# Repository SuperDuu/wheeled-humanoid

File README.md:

# Wheeled Humanoid Robot (V2)

A custom-designed wheeled humanoid robot featuring a mobile base, dual humanoid arms, custom cycloidal drives, custom motor drivers, and integrated with ROS 2, Computer Vision, and AI.

## Project Structure

- **docs/**: Project documentation, communication protocols, and datasheets.
- **hardware/**: Mechanical CAD designs (SolidWorks/STEP) and electronic PCBs (KiCad).
- **firmware/**: Low-level MCU source code for controllers and motor drivers.
- **software/**: High-level ROS 2 packages and AI/Vision algorithms.
- **legacy/**: Submodule containing Version 1 of the AGV project (`agv_project`).

## Quick Start

### Submodule Initialization
If you just cloned this repository, initialize the legacy v1 submodule:
```bash
git submodule update --init --recursive
```

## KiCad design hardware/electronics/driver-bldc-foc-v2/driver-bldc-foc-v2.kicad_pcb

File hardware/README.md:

# Hardware Designs

This directory contains mechanical and electrical engineering designs.

- **mechanical/**: CAD models, cycloidal gear designs, assembly models, and 3D print files.
- **electronics/**: KiCad schematics and layout designs for custom motor drivers and power boards.

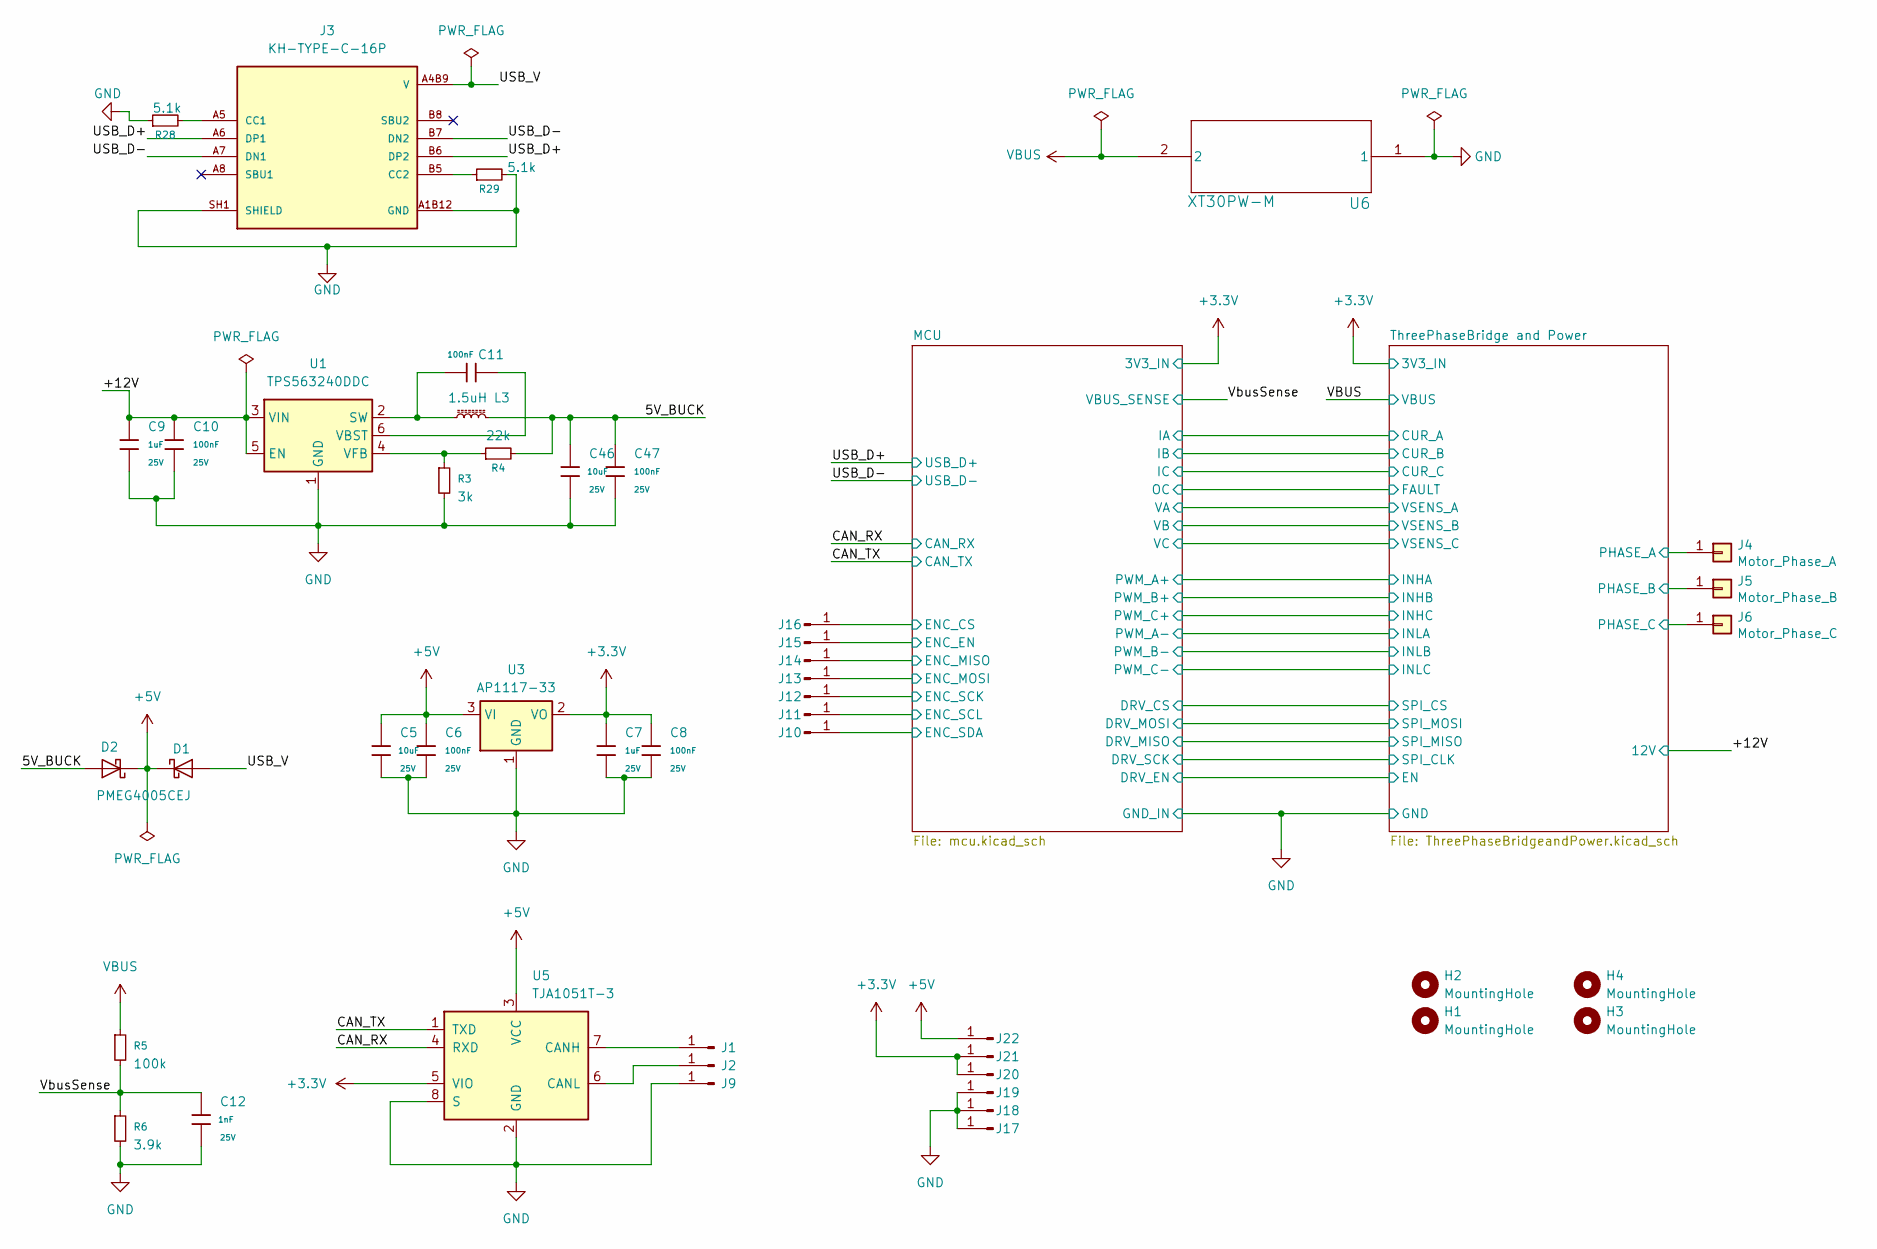
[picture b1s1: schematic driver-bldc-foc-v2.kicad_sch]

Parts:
C5, C46: 10uF; C_0805_2012Metric; Voltage Rated 25V; Tolerance ±10%; Part CL21A106KAYNNNE; LCSC C15850
C6, C8, C10, C11, C47: 100nF; C_0805_2012Metric; Voltage Rated 25V; Tolerance ±10%; Part CL21A106KAYNNNE; LCSC C15850
C7, C9: 1uF; C_0805_2012Metric; Voltage Rated 25V; Tolerance ±10%; Part CL21A106KAYNNNE; LCSC C15850
C12: 1nF; C_0805_2012Metric; Voltage Rated 25V; Tolerance ±10%; Part CL21A106KAYNNNE; LCSC C15850
D1, D2: PMEG4005CEJ; D_SOD-323F
H1, H2, H3, H4: MountingHole; MountingHole_3.2mm_M3_ISO7380_Pad_TopBottom
J1, J2, J9, J10, J11, J12, J13, J14, J15, J16, J17, J18, J19, J20, J21, J22: Conn_01x01_Pin; SolderWirePad_1x01_SMD_2x4mm
J3: KH-TYPE-C-16P; KINGHELM_KH-TYPE-C-16P; PARTREV A0
J4: Motor_Phase_A; SolderWirePad_1x01_SMD_5x10mm
J5: Motor_Phase_B; SolderWirePad_1x01_SMD_5x10mm
J6: Motor_Phase_C; SolderWirePad_1x01_SMD_5x10mm
L3: 1.5uH; L_APV_ANR5040
R3: 3k; R_0805_2012Metric
R4: 22k; R_0805_2012Metric
R5: 100k; R_0805_2012Metric
R6: 3.9k; R_0805_2012Metric
R28, R29: 5.1k; R_0805_2012Metric
U1: TPS563240DDC; SOT-23-6
U3: AP1117-33; SOT-223-3_TabPin2
U5: TJA1051T-3; SOIC-8_3.9x4.9mm_P1.27mm
U6: XT30PW-M; XT30PW-M_AMA

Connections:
+3.3V: C7.1, C8.1, J20.1 (Pin_1_1), J21.1 (Pin_1_1), U3.2 (VO), U5.5 (VIO); also elsewhere on the board
+5V: C5.1, C6.1, D1.1 (K), D2.1 (K), J22.1 (Pin_1_1), U3.3 (VI), U5.3 (VCC)
/5V_BUCK: C46.1, C47.1, D2.2 (A), L3.2, R4.2
/+12V: C9.1, C10.1, U1.3 (VIN), U1.5 (EN); also elsewhere on the board
/CAN_RX: U5.4 (RXD); also elsewhere on the board
/CAN_TX: U5.1 (TXD); also elsewhere on the board
/MCU/ENC_CS: J16.1 (Pin_1_1); also elsewhere on the board
/MCU/ENC_EN: J15.1 (Pin_1_1); also elsewhere on the board
/MCU/ENC_MISO: J14.1 (Pin_1_1); also elsewhere on the board
/MCU/ENC_MOSI: J13.1 (Pin_1_1); also elsewhere on the board
/MCU/ENC_SCK: J12.1 (Pin_1_1); also elsewhere on the board
/MCU/ENC_SCL: J11.1 (Pin_1_1); also elsewhere on the board
/MCU/ENC_SDA: J10.1 (Pin_1_1); also elsewhere on the board
/ThreePhaseBridge and Power/SHA: J4.1 (Pin_1_1); also elsewhere on the board
/ThreePhaseBridge and Power/SHB: J5.1 (Pin_1_1); also elsewhere on the board
/ThreePhaseBridge and Power/SHC: J6.1 (Pin_1_1); also elsewhere on the board
/USB_D+: J3.A6 (DP1), J3.B6 (DP2); also elsewhere on the board
/USB_D-: J3.A7 (DN1), J3.B7 (DN2); also elsewhere on the board
/VbusSense: C12.1, R5.2, R6.1; also elsewhere on the board
GND: C5.2, C6.2, C7.2, C8.2, C9.2, C10.2, C12.2, C46.2, C47.2, J3.A1B12 (GND), J3.A12B1 (GND), J3.SH1 (SHIELD), J3.SH2 (SHIELD), J3.SH3 (SHIELD), J3.SH4 (SHIELD), J9.1 (Pin_1_1), J17.1 (Pin_1_1), J18.1 (Pin_1_1), J19.1 (Pin_1_1), R3.2, R6.2, R28.1, R29.2, U1.1 (GND), U3.1 (GND), U5.2 (GND), U5.8 (S), U6.1; also elsewhere on the board
unnamed: J1.1 (Pin_1_1), U5.7 (CANH)
unnamed: J2.1 (Pin_1_1), U5.6 (CANL)
unnamed: J3.A5 (CC1), R28.2
unnamed: J3.B5 (CC2), R29.1
unnamed: C11.2, L3.1, U1.2 (SW)
unnamed: C11.1, U1.6 (VBST)
unnamed: R3.1, R4.1, U1.4 (VFB)
V: D1.2 (A), J3.A4B9 (V), J3.A9B4 (V)
VBUS: R5.1, U6.2; also elsewhere on the board

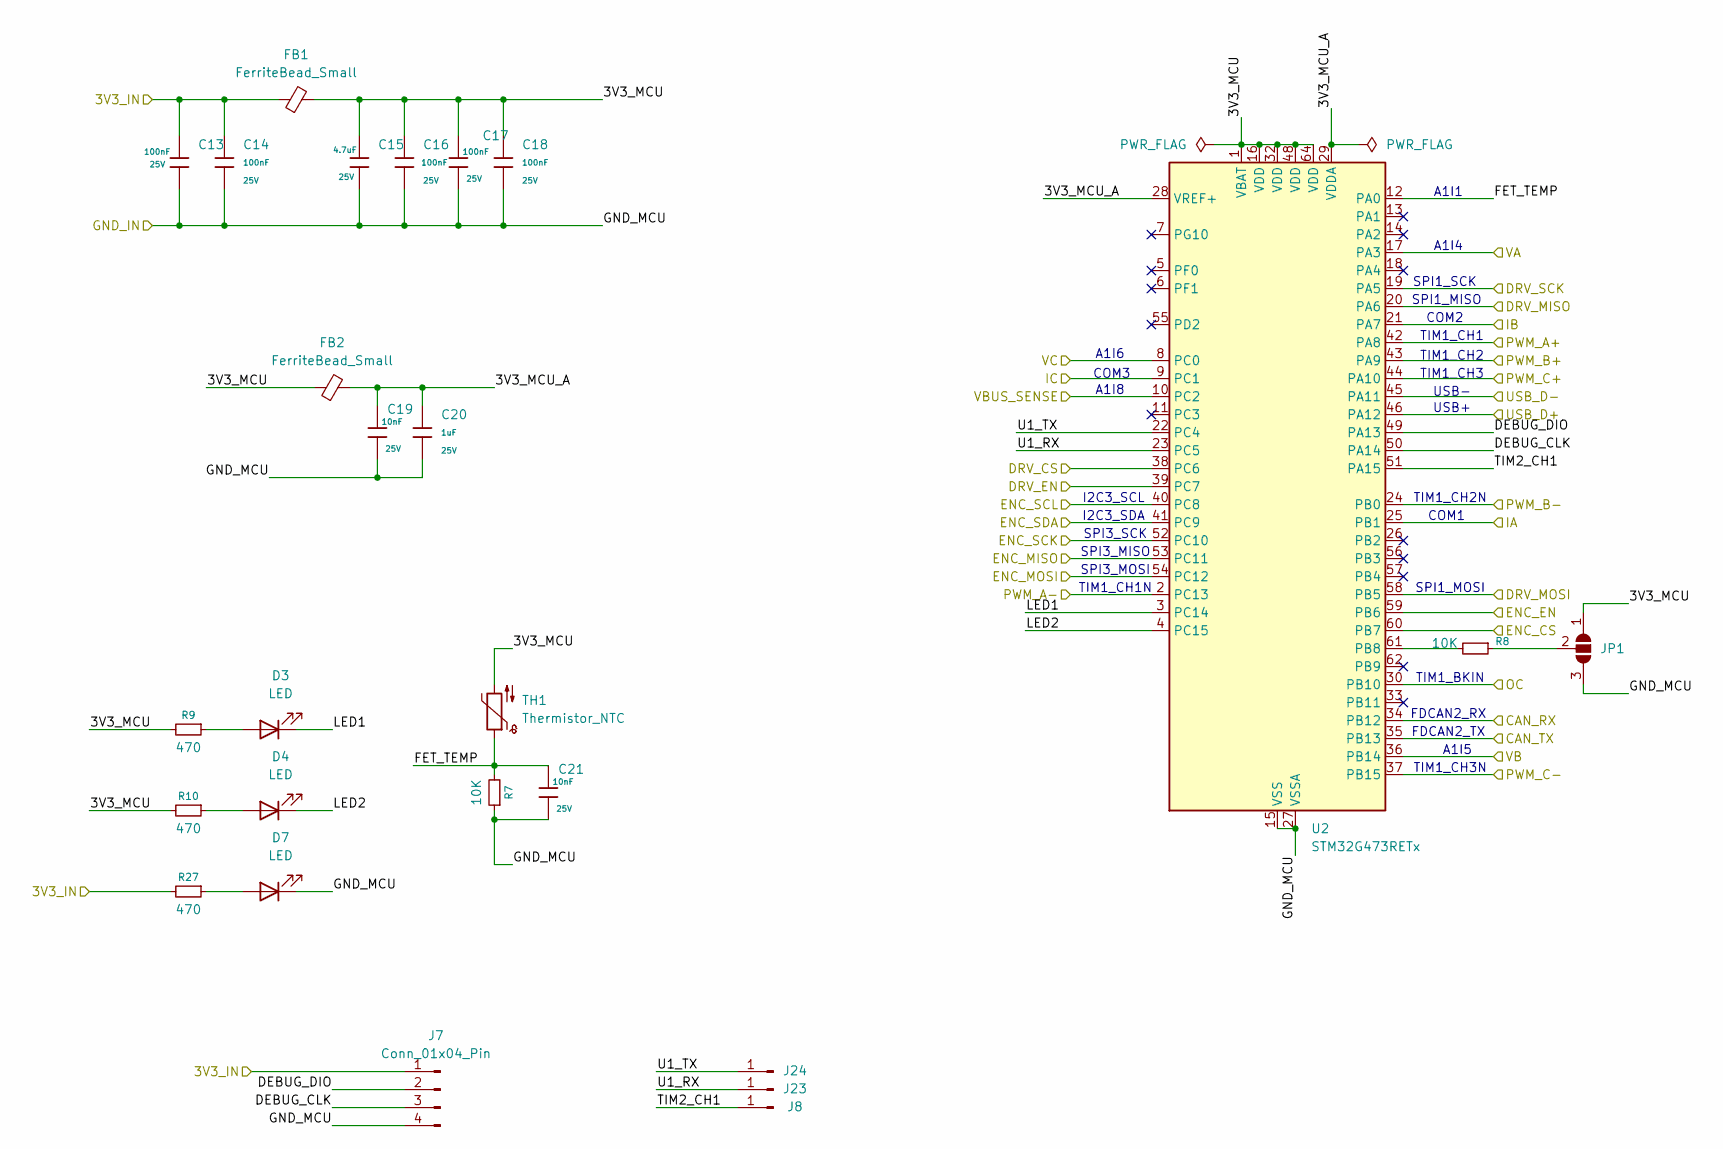
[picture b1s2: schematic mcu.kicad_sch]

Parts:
C13, C14, C16, C17, C18: 100nF; C_0805_2012Metric; Voltage Rated 25V; Tolerance ±10%; Part CL21A106KAYNNNE; LCSC C15850
C15: 4.7uF; C_0805_2012Metric; Voltage Rated 25V; Tolerance ±10%; Part CL21A106KAYNNNE; LCSC C15850
C19, C21: 10nF; C_0805_2012Metric; Voltage Rated 25V; Tolerance ±10%; Part CL21A106KAYNNNE; LCSC C15850
C20: 1uF; C_0805_2012Metric; Voltage Rated 25V; Tolerance ±10%; Part CL21A106KAYNNNE; LCSC C15850
D3, D4, D7: LED; LED_0805_2012Metric
FB1, FB2: FerriteBead_Small; L_0603_1608Metric_Pad1.05x0.95mm_HandSolder
J7: Conn_01x04_Pin; JST_XH_B4B-XH-A_1x04_P2.50mm_Vertical
J8, J23, J24: Conn_01x01_Pin; SolderWirePad_1x01_SMD_1x2mm
JP1: SolderJumper_3_Open; SolderJumper-3_P1.3mm_Open_RoundedPad1.0x1.5mm_NumberLabels
R7, R8: 10K; R_0805_2012Metric
R9, R10, R27: 470; R_0805_2012Metric
TH1: Thermistor_NTC; R_Axial_DIN0204_L3.6mm_D1.6mm_P1.90mm_Vertical
U2: STM32G473RETx; LQFP-64_10x10mm_P0.5mm

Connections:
+3.3V: C13.1, C14.1, FB1.1, J7.1, R27.2; also elsewhere on the board
/CAN_RX: U2.34 (PB12); also elsewhere on the board
/CAN_TX: U2.35 (PB13); also elsewhere on the board
/MCU/3V3_MCU: C15.1, C16.1, C17.1, C18.1, FB1.2, FB2.1, JP1.1 (A), R9.2, R10.2, TH1.2, U2.1 (VBAT), U2.16 (VDD), U2.32 (VDD), U2.48 (VDD), U2.64 (VDD)
/MCU/3V3_MCU_A: C19.1, C20.1, FB2.2, U2.28 (VREF+), U2.29 (VDDA)
/MCU/DEBUG_CLK: J7.3, U2.50 (PA14)
/MCU/DEBUG_DIO: J7.2, U2.49 (PA13)
/MCU/DRV_CS: U2.38 (PC6); also elsewhere on the board
/MCU/DRV_EN: U2.39 (PC7); also elsewhere on the board
/MCU/DRV_MISO: U2.20 (PA6); also elsewhere on the board
/MCU/DRV_MOSI: U2.58 (PB5); also elsewhere on the board
/MCU/DRV_SCK: U2.19 (PA5); also elsewhere on the board
/MCU/ENC_CS: U2.60 (PB7); also elsewhere on the board
/MCU/ENC_EN: U2.59 (PB6); also elsewhere on the board
/MCU/ENC_MISO: U2.53 (PC11); also elsewhere on the board
/MCU/ENC_MOSI: U2.54 (PC12); also elsewhere on the board
/MCU/ENC_SCK: U2.52 (PC10); also elsewhere on the board
/MCU/ENC_SCL: U2.40 (PC8); also elsewhere on the board
/MCU/ENC_SDA: U2.41 (PC9); also elsewhere on the board
/MCU/FET_TEMP: C21.1, R7.2, TH1.1, U2.12 (PA0)
/MCU/IA: U2.25 (PB1); also elsewhere on the board
/MCU/IB: U2.21 (PA7); also elsewhere on the board
/MCU/IC: U2.9 (PC1); also elsewhere on the board
/MCU/LED1: D3.1 (K), U2.3 (PC14)
/MCU/LED2: D4.1 (K), U2.4 (PC15)
/MCU/OC: U2.30 (PB10); also elsewhere on the board
/MCU/PWM_A+: U2.42 (PA8); also elsewhere on the board
/MCU/PWM_A-: U2.2 (PC13); also elsewhere on the board
/MCU/PWM_B+: U2.43 (PA9); also elsewhere on the board
/MCU/PWM_B-: U2.24 (PB0); also elsewhere on the board
/MCU/PWM_C+: U2.44 (PA10); also elsewhere on the board
/MCU/PWM_C-: U2.37 (PB15); also elsewhere on the board
/MCU/TIM2_CH1: J8.1 (Pin_1_1), U2.51 (PA15)
/MCU/U1_RX: J23.1 (Pin_1_1), U2.23 (PC5)
/MCU/U1_TX: J24.1 (Pin_1_1), U2.22 (PC4)
/MCU/VA: U2.17 (PA3); also elsewhere on the board
/MCU/VB: U2.36 (PB14); also elsewhere on the board
/MCU/VC: U2.8 (PC0); also elsewhere on the board
/USB_D+: U2.46 (PA12); also elsewhere on the board
/USB_D-: U2.45 (PA11); also elsewhere on the board
/VbusSense: U2.10 (PC2); also elsewhere on the board
GND: C13.2, C14.2, C15.2, C16.2, C17.2, C18.2, C19.2, C20.2, C21.2, D7.1 (K), J7.4, JP1.3 (B), R7.1, U2.15 (VSS), U2.27 (VSSA), U2.31 (VSS), U2.47 (VSS), U2.63 (VSS); also elsewhere on the board
unnamed: D3.2 (A), R9.1
unnamed: D4.2 (A), R10.1
unnamed: D7.2 (A), R27.1
unnamed: JP1.2 (C), R8.1
unnamed: R8.2, U2.61 (PB8)

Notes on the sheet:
I2C3_SDA
SPI3_MOSI
TIM1_CH2N
SPI1_SCK
SPI3_SCK
TIM1_CH3N
A1I6
SPI1_MISO
SPI1_MOSI
A1I1
TIM1_CH3
TIM1_BKIN
A1I4
COM2
COM3
USB-
I2C3_SCL
FDCAN2_RX
FDCAN2_TX
USB+
TIM1_CH1N
TIM1_CH1
A1I5
A1I8
SPI3_MISO
TIM1_CH2
COM1

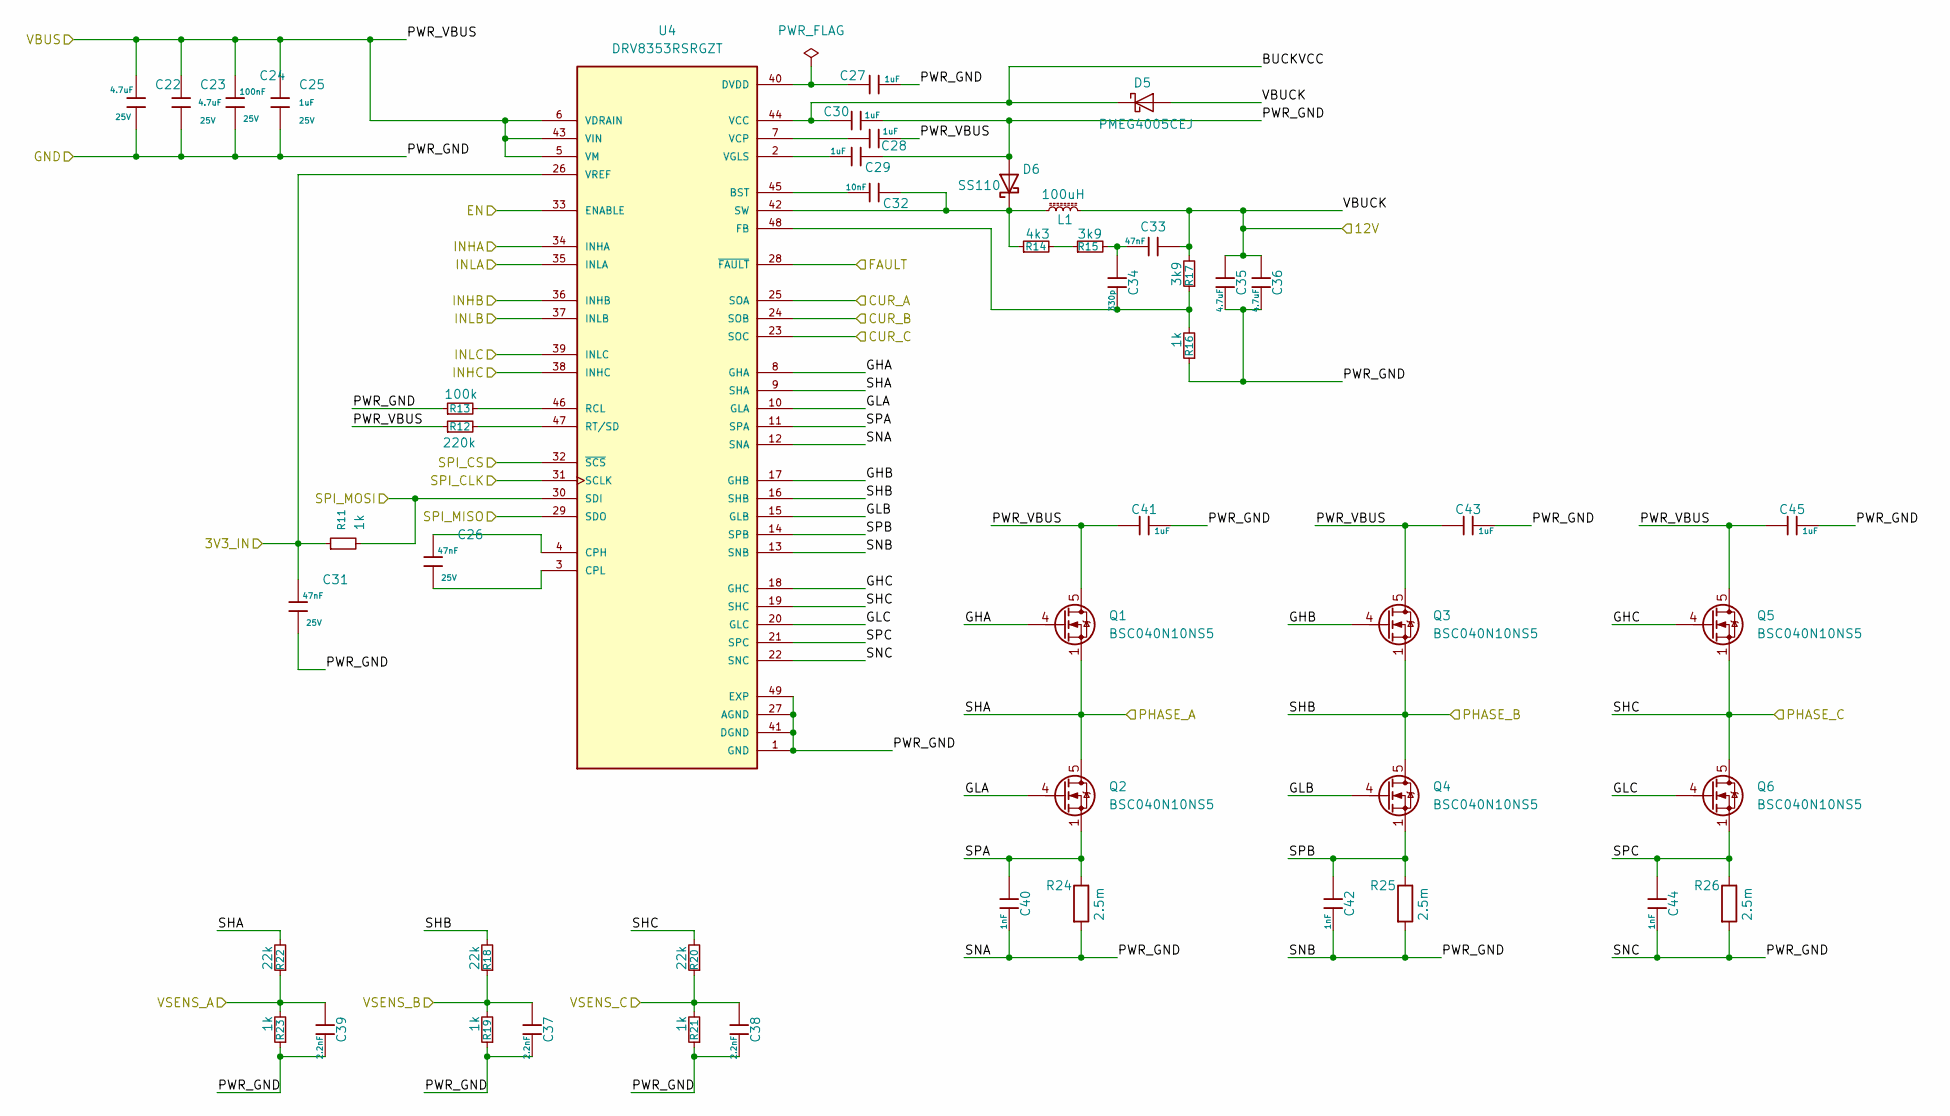
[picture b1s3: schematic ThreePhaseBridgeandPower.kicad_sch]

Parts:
C22, C23: 4.7uF; C_1210_3225Metric; Voltage Rated 25V; Tolerance ±10%; Part CL21A106KAYNNNE; LCSC C15850
C24: 100nF; C_0805_2012Metric; Voltage Rated 25V; Tolerance ±10%; Part CL21A106KAYNNNE; LCSC C15850
C25: 1uF; C_1210_3225Metric; Voltage Rated 25V; Tolerance ±10%; Part CL21A106KAYNNNE; LCSC C15850
C26, C31, C33: 47nF; C_0805_2012Metric; Voltage Rated 25V; Tolerance ±10%; Part CL21A106KAYNNNE; LCSC C15850
C27, C28, C29, C30: 1uF; C_0805_2012Metric; Voltage Rated 25V; Tolerance ±10%; Part CL21A106KAYNNNE; LCSC C15850
C32: 10nF; C_0805_2012Metric; Voltage Rated 25V; Tolerance ±10%; Part CL21A106KAYNNNE; LCSC C15850
C34: 330p; C_0805_2012Metric; Voltage Rated 25V; Tolerance ±10%; Part CL21A106KAYNNNE; LCSC C15850
C35, C36: 4.7uF; C_0805_2012Metric; Voltage Rated 25V; Tolerance ±10%; Part CL21A106KAYNNNE; LCSC C15850
C37, C38, C39: 2.2nF; C_0805_2012Metric; Voltage Rated 25V; Tolerance ±10%; Part CL21A106KAYNNNE; LCSC C15850
C40, C42, C44: 1nF; C_0805_2012Metric; Voltage Rated 25V; Tolerance ±10%; Part CL21A106KAYNNNE; LCSC C15850
C41, C43, C45: 1uF; C_1206_3216Metric; Voltage Rated 25V; Tolerance ±10%; Part CL21A106KAYNNNE; LCSC C15850
D5: PMEG4005CEJ; D_SOD-323F
D6: SS110; D_SMA
L1: 100uH; L_Cenker_CKCS8040
Q1, Q2, Q3, Q4, Q5, Q6: BSC040N10NS5; TDSON-8-1
R11, R16, R19, R21, R23: 1k; R_0805_2012Metric
R12: 220k; R_0805_2012Metric
R13: 100k; R_0805_2012Metric
R14: 4k3; R_0805_2012Metric
R15, R17: 3k9; R_0805_2012Metric
R18, R20, R22: 22k; R_0805_2012Metric
R24, R25, R26: 2.5m; R_2512_6332Metric
U4: DRV8353RSRGZT; QFN50P700X700X100-49N; PARTREV A

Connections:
+3.3V: C31.1, R11.1, U4.26 (VREF); also elsewhere on the board
/+12V: C33.2, C35.2, C36.2, D5.2 (A), L1.2, R17.2; also elsewhere on the board
/MCU/DRV_CS: U4.32 (~SCS); also elsewhere on the board
/MCU/DRV_EN: U4.33 (ENABLE); also elsewhere on the board
/MCU/DRV_MISO: U4.29 (SDO); also elsewhere on the board
/MCU/DRV_MOSI: R11.2, U4.30 (SDI); also elsewhere on the board
/MCU/DRV_SCK: U4.31 (SCLK); also elsewhere on the board
/MCU/IA: U4.25 (SOA); also elsewhere on the board
/MCU/IB: U4.24 (SOB); also elsewhere on the board
/MCU/IC: U4.23 (SOC); also elsewhere on the board
/MCU/OC: U4.28 (~FAULT); also elsewhere on the board
/MCU/PWM_A+: U4.34 (INHA); also elsewhere on the board
/MCU/PWM_A-: U4.35 (INLA); also elsewhere on the board
/MCU/PWM_B+: U4.36 (INHB); also elsewhere on the board
/MCU/PWM_B-: U4.37 (INLB); also elsewhere on the board
/MCU/PWM_C+: U4.38 (INHC); also elsewhere on the board
/MCU/PWM_C-: U4.39 (INLC); also elsewhere on the board
/MCU/VA: C39.2, R22.1, R23.2; also elsewhere on the board
/MCU/VB: C37.2, R18.1, R19.2; also elsewhere on the board
/MCU/VC: C38.2, R20.1, R21.2; also elsewhere on the board
/ThreePhaseBridge and Power/BUCKVCC: C30.1, D5.1 (K), U4.44 (VCC)
/ThreePhaseBridge and Power/GHA: Q1.4 (G), U4.8 (GHA)
/ThreePhaseBridge and Power/GHB: Q3.4 (G), U4.17 (GHB)
/ThreePhaseBridge and Power/GHC: Q5.4 (G), U4.18 (GHC)
/ThreePhaseBridge and Power/GLA: Q2.4 (G), U4.10 (GLA)
/ThreePhaseBridge and Power/GLB: Q4.4 (G), U4.15 (GLB)
/ThreePhaseBridge and Power/GLC: Q6.4 (G), U4.20 (GLC)
/ThreePhaseBridge and Power/SHA: Q1.1 (S), Q1.2 (S), Q1.3 (S), Q2.5 (D), R22.2, U4.9 (SHA); also elsewhere on the board
/ThreePhaseBridge and Power/SHB: Q3.1 (S), Q3.2 (S), Q3.3 (S), Q4.5 (D), R18.2, U4.16 (SHB); also elsewhere on the board
/ThreePhaseBridge and Power/SHC: Q5.1 (S), Q5.2 (S), Q5.3 (S), Q6.5 (D), R20.2, U4.19 (SHC); also elsewhere on the board
/ThreePhaseBridge and Power/SPA: C40.2, Q2.1 (S), Q2.2 (S), Q2.3 (S), R24.1, U4.11 (SPA)
/ThreePhaseBridge and Power/SPB: C42.2, Q4.1 (S), Q4.2 (S), Q4.3 (S), R25.1, U4.14 (SPB)
/ThreePhaseBridge and Power/SPC: C44.2, Q6.1 (S), Q6.2 (S), Q6.3 (S), R26.1, U4.21 (SPC)
GND: C22.2, C23.2, C24.2, C25.2, C27.2, C29.2, C30.2, C31.2, C35.1, C36.1, C37.1, C38.1, C39.1, C40.1, C41.1, C42.1, C43.1, C44.1, C45.1, D6.2 (A), R13.1, R16.1, R19.1, R21.1, R23.1, R24.2, R25.2, R26.2, U4.1 (GND), U4.12 (SNA), U4.13 (SNB), U4.22 (SNC), U4.27 (AGND), U4.41 (DGND), U4.49 (EXP); also elsewhere on the board
unnamed: C33.1, C34.2, R15.2
unnamed: C32.2, D6.1 (K), L1.1, R14.1, U4.42 (SW)
unnamed: R14.2, R15.1
unnamed: C32.1, U4.45 (BST)
unnamed: C26.1, U4.4 (CPH)
unnamed: C26.2, U4.3 (CPL)
unnamed: C27.1, U4.40 (DVDD)
unnamed: C34.1, R16.2, R17.1, U4.48 (FB)
unnamed: R13.2, U4.46 (RCL)
unnamed: R12.2, U4.47 (RT/SD)
unnamed: C28.1, U4.7 (VCP)
unnamed: C29.1, U4.2 (VGLS)
VBUS: C22.1, C23.1, C24.1, C25.1, C28.2, C41.2, C43.2, C45.2, Q1.5 (D), Q3.5 (D), Q5.5 (D), R12.1, U4.5 (VM), U4.6 (VDRAIN), U4.43 (VIN); also elsewhere on the board

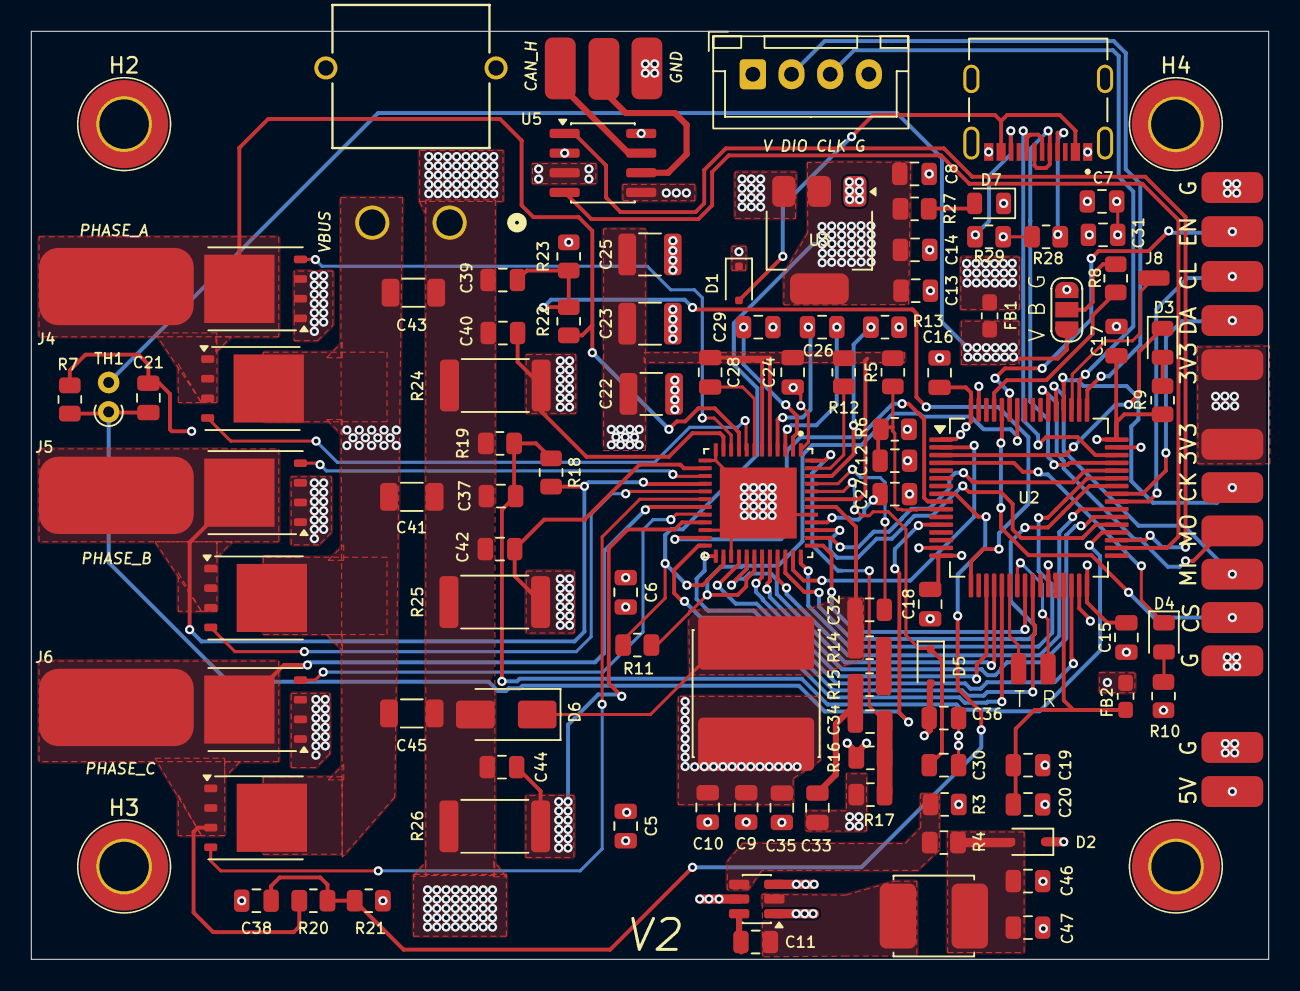
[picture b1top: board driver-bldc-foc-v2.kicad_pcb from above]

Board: 4 copper layers, 80.0 x 60.0 mm, 123 parts (0 on the bottom side), 84 nets.

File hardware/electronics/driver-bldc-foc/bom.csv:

"Refs","Value","Footprint","Qty","DNP"
"C5","10uF","Capacitor_SMD:C_0805_2012Metric","1",""
"C6","100nF","Capacitor_SMD:C_0805_2012Metric","1",""
"C7","1uF","Capacitor_SMD:C_0805_2012Metric","1",""
"C8","100nF","Capacitor_SMD:C_0805_2012Metric","1",""
"C9","1uF","Capacitor_SMD:C_0805_2012Metric","1",""
"C10","100nF","Capacitor_SMD:C_0805_2012Metric","1",""
"C11","100nF","Capacitor_SMD:C_0805_2012Metric","1",""
"C12","1nF","Capacitor_SMD:C_0805_2012Metric","1",""
"C13","100nF","Capacitor_SMD:C_0805_2012Metric","1",""
"C14","100nF","Capacitor_SMD:C_0805_2012Metric","1",""
"C15","4.7uF","Capacitor_SMD:C_0805_2012Metric","1",""
"C16","100nF","Capacitor_SMD:C_0805_2012Metric","1",""
"C17","100nF","Capacitor_SMD:C_0805_2012Metric","1",""
"C18","100nF","Capacitor_SMD:C_0805_2012Metric","1",""
"C19","10nF","Capacitor_SMD:C_0805_2012Metric","1",""
"C20","1uF","Capacitor_SMD:C_0805_2012Metric","1",""
"C21","10nF","Capacitor_SMD:C_0805_2012Metric","1",""
"C22","4.7uF","Capacitor_SMD:C_1210_3225Metric","1",""
"C23","4.7uF","Capacitor_SMD:C_1210_3225Metric","1",""
"C24","100nF","Capacitor_SMD:C_0805_2012Metric","1",""
"C25","1uF","Capacitor_SMD:C_1210_3225Metric","1",""
"C26","47nF","Capacitor_SMD:C_0805_2012Metric","1",""
"C27","1uF","Capacitor_SMD:C_0805_2012Metric","1",""
"C28","1uF","Capacitor_SMD:C_0805_2012Metric","1",""
"C29","1uF","Capacitor_SMD:C_0805_2012Metric","1",""
"C30","1uF","Capacitor_SMD:C_0805_2012Metric","1",""
"C31","47nF","Capacitor_SMD:C_0805_2012Metric","1",""
"C32","10nF","Capacitor_SMD:C_0805_2012Metric","1",""
"C33","47nF","Capacitor_SMD:C_0805_2012Metric","1",""
"C34","330p","Capacitor_SMD:C_0805_2012Metric","1",""
"C35","4.7uF","Capacitor_SMD:C_0805_2012Metric","1",""
"C36","4.7uF","Capacitor_SMD:C_0805_2012Metric","1",""
"C37","2.2nF","Capacitor_SMD:C_0805_2012Metric","1",""
"C38","2.2nF","Capacitor_SMD:C_0805_2012Metric","1",""
"C39","2.2nF","Capacitor_SMD:C_0805_2012Metric","1",""
"C40","1nF","Capacitor_SMD:C_0805_2012Metric","1",""
"C41","1uF","Capacitor_SMD:C_1206_3216Metric","1",""
"C42","1nF","Capacitor_SMD:C_0805_2012Metric","1",""
"C43","1uF","Capacitor_SMD:C_1206_3216Metric","1",""
"C44","1nF","Capacitor_SMD:C_0805_2012Metric","1",""
"C45","1uF","Capacitor_SMD:C_1206_3216Metric","1",""
"D1","PMEG4005CEJ","Diode_SMD:D_SOD-323F","1",""
"D2","PMEG4005CEJ","Diode_SMD:D_SOD-323F","1",""
"D3","LED","LED_SMD:LED_0805_2012Metric","1",""
"D4","LED","LED_SMD:LED_0805_2012Metric","1",""
"D5","PMEG4005CEJ","Diode_SMD:D_SOD-323F","1",""
"D6","SS110","Diode_SMD:D_SMA","1",""
"D7","LED","LED_SMD:LED_0805_2012Metric","1",""
"FB1","FerriteBead_Small","Inductor_SMD:L_0603_1608Metric_Pad1.05x0.95mm_HandSolder","1",""
"FB2","FerriteBead_Small","Inductor_SMD:L_0603_1608Metric_Pad1.05x0.95mm_HandSolder","1",""
"J1","Conn_01x01_Pin","Connector_Wire:SolderWirePad_1x01_SMD_2x4mm","1",""
"J2","Conn_01x01_Pin","Connector_Wire:SolderWirePad_1x01_SMD_2x4mm","1",""
"J3","KH-TYPE-C-16P","KH-TYPE-C-16P:KINGHELM_KH-TYPE-C-16P","1",""
"J4","Motor_Phase_A","Connector_Wire:SolderWirePad_1x01_SMD_5x10mm","1",""
"J5","Motor_Phase_B","Connector_Wire:SolderWirePad_1x01_SMD_5x10mm","1",""
"J6","Motor_Phase_C","Connector_Wire:SolderWirePad_1x01_SMD_5x10mm","1",""
"J7","Conn_01x04_Pin","Connector_JST:JST_XH_B4B-XH-A_1x04_P2.50mm_Vertical","1",""
"J8","Conn_01x01_Pin","Connector_Wire:SolderWirePad_1x01_SMD_1x2mm","1",""
"J9","Conn_01x01_Pin","Connector_Wire:SolderWirePad_1x01_SMD_2x4mm","1",""
"J10","Conn_01x01_Pin","Connector_Wire:SolderWirePad_1x01_SMD_2x4mm","1",""
"J11","Conn_01x01_Pin","Connector_Wire:SolderWirePad_1x01_SMD_2x4mm","1",""
"J12","Conn_01x01_Pin","Connector_Wire:SolderWirePad_1x01_SMD_2x4mm","1",""
"J13","Conn_01x01_Pin","Connector_Wire:SolderWirePad_1x01_SMD_2x4mm","1",""
"J14","Conn_01x01_Pin","Connector_Wire:SolderWirePad_1x01_SMD_2x4mm","1",""
"J15","Conn_01x01_Pin","Connector_Wire:SolderWirePad_1x01_SMD_2x4mm","1",""
"J16","Conn_01x01_Pin","Connector_Wire:SolderWirePad_1x01_SMD_2x4mm","1",""
"J17","Conn_01x01_Pin","Connector_Wire:SolderWirePad_1x01_SMD_2x4mm","1",""
"J18","Conn_01x01_Pin","Connector_Wire:SolderWirePad_1x01_SMD_2x4mm","1",""
"J19","Conn_01x01_Pin","Connector_Wire:SolderWirePad_1x01_SMD_2x4mm","1",""
"J20","Conn_01x01_Pin","Connector_Wire:SolderWirePad_1x01_SMD_2x4mm","1",""
"J21","Conn_01x01_Pin","Connector_Wire:SolderWirePad_1x01_SMD_2x4mm","1",""
"J22","Conn_01x01_Pin","Connector_Wire:SolderWirePad_1x01_SMD_2x4mm","1",""
"J23","Conn_01x01_Pin","Connector_Wire:SolderWirePad_1x01_SMD_1x2mm","1",""
"J24","Conn_01x01_Pin","Connector_Wire:SolderWirePad_1x01_SMD_1x2mm","1",""
"L1","100uH","Inductor_SMD:L_Cenker_CKCS8040","1",""
"L3","1.5uH","Inductor_SMD:L_APV_ANR5040","1",""
"Q1","BSC040N10NS5","Package_TO_SOT_SMD:TDSON-8-1","1",""
"Q2","BSC040N10NS5","Package_TO_SOT_SMD:TDSON-8-1","1",""
"Q3","BSC040N10NS5","Package_TO_SOT_SMD:TDSON-8-1","1",""
"Q4","BSC040N10NS5","Package_TO_SOT_SMD:TDSON-8-1","1",""
"Q5","BSC040N10NS5","Package_TO_SOT_SMD:TDSON-8-1","1",""
"Q6","BSC040N10NS5","Package_TO_SOT_SMD:TDSON-8-1","1",""
"R3","3k","Resistor_SMD:R_0805_2012Metric","1",""
"R4","22k","Resistor_SMD:R_0805_2012Metric","1",""
"R5","100k","Resistor_SMD:R_0805_2012Metric","1",""
"R6","3.9k","Resistor_SMD:R_0805_2012Metric","1",""
"R7","10K","Resistor_SMD:R_0805_2012Metric","1",""
"R8","10K","Resistor_SMD:R_0805_2012Metric","1",""
"R9","470","Resistor_SMD:R_0805_2012Metric","1",""
"R10","470","Resistor_SMD:R_0805_2012Metric","1",""
"R11","1k","Resistor_SMD:R_0805_2012Metric","1",""
"R12","220k","Resistor_SMD:R_0805_2012Metric","1",""
"R13","100k","Resistor_SMD:R_0805_2012Metric","1",""
"R14","4k3","Resistor_SMD:R_0805_2012Metric","1",""
"R15","3k9","Resistor_SMD:R_0805_2012Metric","1",""
"R16","1k","Resistor_SMD:R_0805_2012Metric","1",""
"R17","3k9","Resistor_SMD:R_0805_2012Metric","1",""
"R18","22k","Resistor_SMD:R_0805_2012Metric","1",""
"R19","1k","Resistor_SMD:R_0805_2012Metric","1",""
"R20","22k","Resistor_SMD:R_0805_2012Metric","1",""
"R21","1k","Resistor_SMD:R_0805_2012Metric","1",""
"R22","22k","Resistor_SMD:R_0805_2012Metric","1",""
"R23","1k","Resistor_SMD:R_0805_2012Metric","1",""
"R24","2.5m","Resistor_SMD:R_2512_6332Metric","1",""
"R25","2.5m","Resistor_SMD:R_2512_6332Metric","1",""
"R26","2.5m","Resistor_SMD:R_2512_6332Metric","1",""
"R27","470","Resistor_SMD:R_0805_2012Metric","1",""
"R28","5.1k","Resistor_SMD:R_0805_2012Metric","1",""
"R29","5.1k","Resistor_SMD:R_0805_2012Metric","1",""
"TH1","Thermistor_NTC","Resistor_THT:R_Axial_DIN0204_L3.6mm_D1.6mm_P1.90mm_Vertical","1",""
"U1","TPS563240DDC","Package_TO_SOT_SMD:SOT-23-6","1",""
"U2","STM32G473RETx","Package_QFP:LQFP-64_10x10mm_P0.5mm","1",""
"U3","AP1117-33","Package_TO_SOT_SMD:SOT-223-3_TabPin2","1",""
"U4","DRV8353RSRGZT","DRV8353RSRGZT:QFN50P700X700X100-49N","1",""
"U5","TJA1051T-3","Package_SO:SOIC-8_3.9x4.9mm_P1.27mm","1",""
"U6","XT30PW-M","XT30PW-M_AMA","1",""

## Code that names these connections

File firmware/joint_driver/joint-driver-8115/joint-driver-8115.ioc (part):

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Mcu.Name=STM32G473R(B-C-E)Tx
Mcu.Package=LQFP64
Mcu.UserName=STM32G473RETx
PA0.GPIOParameters=GPIO_Label
PA0.GPIO_Label=FET_TEMP
PA0.Mode=IN1-Single-Ended
PA0.Signal=ADC1_IN1
PA10.Signal=S_TIM1_CH3
PA11.Mode=Device
PA11.Signal=USB_DM
PA12.Mode=Device
PA12.Signal=USB_DP
PA13.Mode=Serial_Wire
PA13.Signal=SYS_JTMS-SWDIO
PA14.Mode=Serial_Wire
PA14.Signal=SYS_JTCK-SWCLK
PA15.Signal=S_TIM2_CH1
PA3.GPIOParameters=GPIO_Label
PA3.GPIO_Label=VSENSE_A
PA3.Mode=IN4-Single-Ended
PA3.Signal=ADC1_IN4
PA5.GPIOParameters=GPIO_Label
PA5.GPIO_Label=DRV_SCK
PA5.Mode=Full_Duplex_Master
PA5.Signal=SPI1_SCK
PA6.GPIOParameters=GPIO_Label
PA6.GPIO_Label=DRV_MISO
PA6.Mode=Full_Duplex_Master
PA6.Signal=SPI1_MISO
PA7.Signal=SharedAnalog_PA7
PA8.Signal=S_TIM1_CH1
PA9.Signal=S_TIM1_CH2
PB0.Mode=PWM Generation2 CH2 CH2N
PB0.Signal=TIM1_CH2N
PB1.Signal=SharedAnalog_PB1
PB10.GPIOParameters=GPIO_Label
PB10.GPIO_Label=DRV_BKIN
PB10.Mode=Activate-Break-Input
PB10.Signal=TIM1_BKIN
PB12.GPIOParameters=GPIO_Label
PB12.GPIO_Label=CAN_RX
PB12.Mode=FDCAN_Activate
PB12.Signal=FDCAN2_RX
PB13.GPIOParameters=GPIO_Label
PB13.GPIO_Label=CAN_TX
PB13.Mode=FDCAN_Activate
PB13.Signal=FDCAN2_TX
PB14.GPIOParameters=GPIO_Label
PB14.GPIO_Label=VSENSE_B
PB14.Mode=IN5-Single-Ended
PB14.Signal=ADC1_IN5
PB15.Mode=PWM Generation3 CH3 CH3N
PB15.Signal=TIM1_CH3N
PB5.GPIOParameters=GPIO_Label
PB5.GPIO_Label=DRV_MOSI
PB5.Mode=Full_Duplex_Master
PB5.Signal=SPI1_MOSI
PB6.GPIOParameters=GPIO_Label
PB6.GPIO_Label=ENC_EN
PB6.Signal=GPIO_Output
PB7.GPIOParameters=GPIO_Speed,PinState,GPIO_Label
PB7.GPIO_Label=ENC_CS
PB7.GPIO_Speed=GPIO_SPEED_FREQ_HIGH
PB7.PinState=GPIO_PIN_SET
PB7.Signal=GPIO_Output
PC0.GPIOParameters=GPIO_Label
PC0.GPIO_Label=VSENSE_C
PC0.Mode=IN6-Single-Ended
PC0.Signal=ADC1_IN6
PC1.Signal=SharedAnalog_PC1
PC10.GPIOParameters=GPIO_Label
PC10.GPIO_Label=ENC_SCK
PC10.Mode=Full_Duplex_Master
PC10.Signal=SPI3_SCK
PC11.GPIOParameters=GPIO_Label
PC11.GPIO_Label=ENC_MISO
PC11.Mode=Full_Duplex_Master
PC11.Signal=SPI3_MISO
PC12.GPIOParameters=GPIO_Label
PC12.GPIO_Label=ENC_MOSI
PC12.Mode=Full_Duplex_Master
PC12.Signal=SPI3_MOSI
PC13.Mode=PWM Generation1 CH1 CH1N
PC13.Signal=TIM1_CH1N
PC14-OSC32_IN.GPIOParameters=GPIO_Label
PC14-OSC32_IN.GPIO_Label=LED_1
PC14-OSC32_IN.Signal=GPIO_Output
PC15-OSC32_OUT.GPIOParameters=GPIO_Label
PC15-OSC32_OUT.GPIO_Label=LED_2
PC15-OSC32_OUT.Signal=GPIO_Output
PC2.GPIOParameters=GPIO_Label
PC2.GPIO_Label=VBUS_SENSE
PC2.Mode=IN8-Single-Ended
PC2.Signal=ADC1_IN8
PC4.Mode=Asynchronous
PC4.Signal=USART1_TX
PC5.Mode=Asynchronous
PC5.Signal=USART1_RX
PC6.GPIOParameters=GPIO_Speed,PinState,GPIO_Label
PC6.GPIO_Label=DRV_CS
PC6.GPIO_Speed=GPIO_SPEED_FREQ_HIGH
PC6.PinState=GPIO_PIN_SET
PC6.Signal=GPIO_Output
PC7.GPIOParameters=GPIO_Speed,PinState,GPIO_Label
PC7.GPIO_Label=DRV_EN
PC7.GPIO_Speed=GPIO_SPEED_FREQ_HIGH
PC7.PinState=GPIO_PIN_SET
PC7.Signal=GPIO_Output
PC8.GPIOParameters=GPIO_Label
PC8.GPIO_Label=ENC_SCL
PC8.Mode=I2C
PC8.Signal=I2C3_SCL
PC9.GPIOParameters=GPIO_Label
PC9.GPIO_Label=ENC_SDA
PC9.Mode=I2C
PC9.Signal=I2C3_SDA
RCC.HSE_VALUE=8000000
RCC.SYSCLKFreq_VALUE=170000000
RCC.SYSCLKSource=RCC_SYSCLKSOURCE_PLLCLK
board=custom
